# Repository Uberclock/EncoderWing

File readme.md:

The Uberclock Encoder Wing was designed for use with Papilio (http://papilio.cc) and Smoothiepanel (http://smoothieware.org/smoothiepanel). It features an RGB illuminated click encoder and an illuminated button. It also supports the use of non-illuminated encoders and buttons for making an inexpensive interface.

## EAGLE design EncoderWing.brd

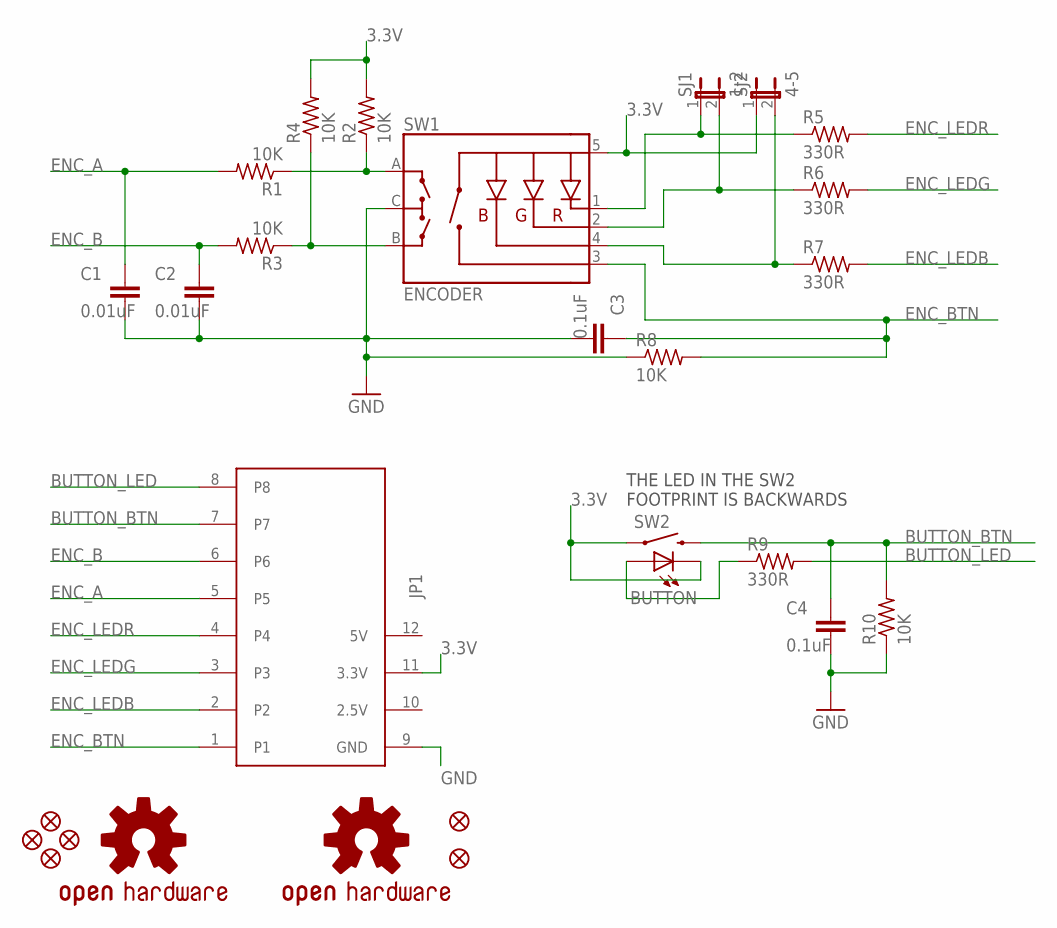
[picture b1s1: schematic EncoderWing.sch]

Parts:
C1, C2: 0.01uF; C0603
C3, C4: 0.1uF; C0603
FID1, FID2, FID3, FID4, FID5, FID6: FIDUCIALUFIDUCIAL; MICRO-FIDUCIAL
JP1: PAPILIO-WING-8BITS
LOGO1, LOGO2: BUTTERFLY_LOGO
R1, R2, R3, R4, R8, R10: 10K; R0603
R5, R6, R7, R9: 330R; R0603
SJ1: 1-2; SJ_2S-NO
SJ2: 4-5; SJ_2S-NO
SW1: ENCODER; ENCODER_LED_3
SW2: BUTTON; TACTILE-PTH-LED-12MM
U$2, U$3: OSHW-LOGOS; OSHW-LOGO-S

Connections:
3.3V: JP1.11 (3.3V), R2.2, R4.2, SJ2.1, SW1.5 (+), SW2.4 (1), SW2.C
BACK_LED_RES: R9.1, SW2.A
BUTTON_BTN: C4.1, JP1.7, R10.2, SW2.2
BUTTON_LED: JP1.8, R9.2
ENC_A: C1.1, JP1.5, R1.2
ENC_A_RES: R1.1, R2.1, SW1.A
ENC_B: C2.1, JP1.6, R3.2
ENC_BTN: C3.1, JP1.1, R8.2, SW1.3 (SW)
ENC_B_RES: R3.1, R4.1, SW1.B
ENC_LEDB: JP1.2, R7.2
ENC_LEDB_RES: R7.1, SJ2.2, SW1.4 (-B)
ENC_LEDG: JP1.3, R6.2
ENC_LEDG_RES: R6.1, SJ1.2, SW1.2 (-G)
ENC_LEDR: JP1.4, R5.2
ENC_LEDR_RES: R5.1, SJ1.1, SW1.1 (-R)
GND: C1.2, C2.2, C3.2, C4.2, JP1.9 (GND), R8.1, R10.1, SW1.C

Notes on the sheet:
THE LED IN THE SW2 FOOTPRINT IS BACKWARDS

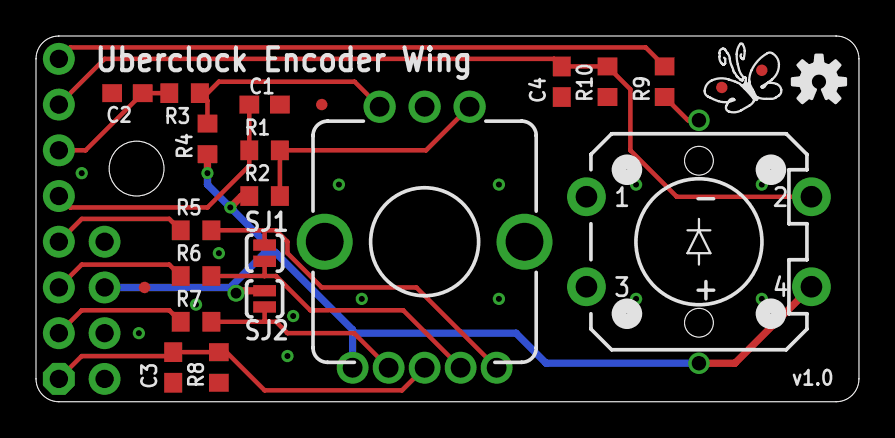
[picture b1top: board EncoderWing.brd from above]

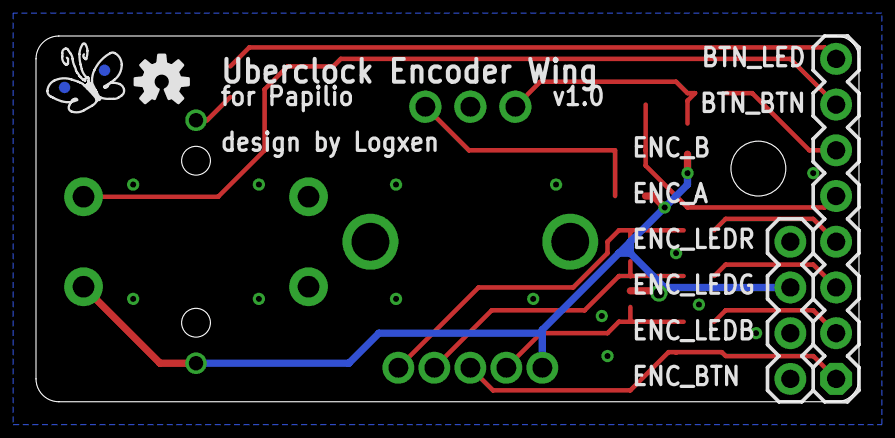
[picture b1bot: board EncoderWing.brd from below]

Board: 2 copper layers, 45.7 x 20.3 mm, 29 parts (4 on the bottom side), 16 nets.

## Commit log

2014-06-17 Initial commit of version 1.0
2014-06-17 Added example Papilio project using Zap 2.3.0
2014-06-17 give debounce a compiler macro and fix read_encoder

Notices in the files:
parts and their libraries:
SparkFun-Aesthetics: Licensing: CC v3.0 Share-Alike You are welcome to use this library for commercial purposes.
